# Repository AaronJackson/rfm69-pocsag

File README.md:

# RFM69 Pager Transmitter

This is a relatively complete project for building a DIY pager transmitter using 
an Adafruit Feather LoRa board and ESP8266. Two microcontrollers are used to enable
full remote shutdown of the transmitter. This repo contains the following,

* Code for an ESP8266, which acts as a bridge between MQTT and the Adafruit LoRa
  board. This simply writes out the MQTT messages to UART.
* Code for an Adafruit LoRa (433MHz variant) board, which configures the RFM69 to
  transmit FSK and perform the POCSAG encoding. This is mostly based around a
  modified [pocsag-tool](https://github.com/hazardousfirmware/pocsag-tool/blob/main/pocsag.c)
  by hazardousfirmware (Thank you!)
* A KiCAD PCB for connecting up the ESP8266 and AdaFruit Feather boards. It includes
  a separate voltage regulator, which taps the 5v from the Feather. The ESP8266 pulls
  the Feather's enable pin to ground, which shuts off its 3.3v regulator.
* A quick laser cut box designed with MakerCase and Inkscape. The final version ended
  up being slightly different I think after some tweaking next to the laser cutter.

I have two deployments of this now:

- At home, using my callsign M6PIU.
- At Nottingham Hackspace, using the FAC callsign MB7PNH (Pager NottingHack).

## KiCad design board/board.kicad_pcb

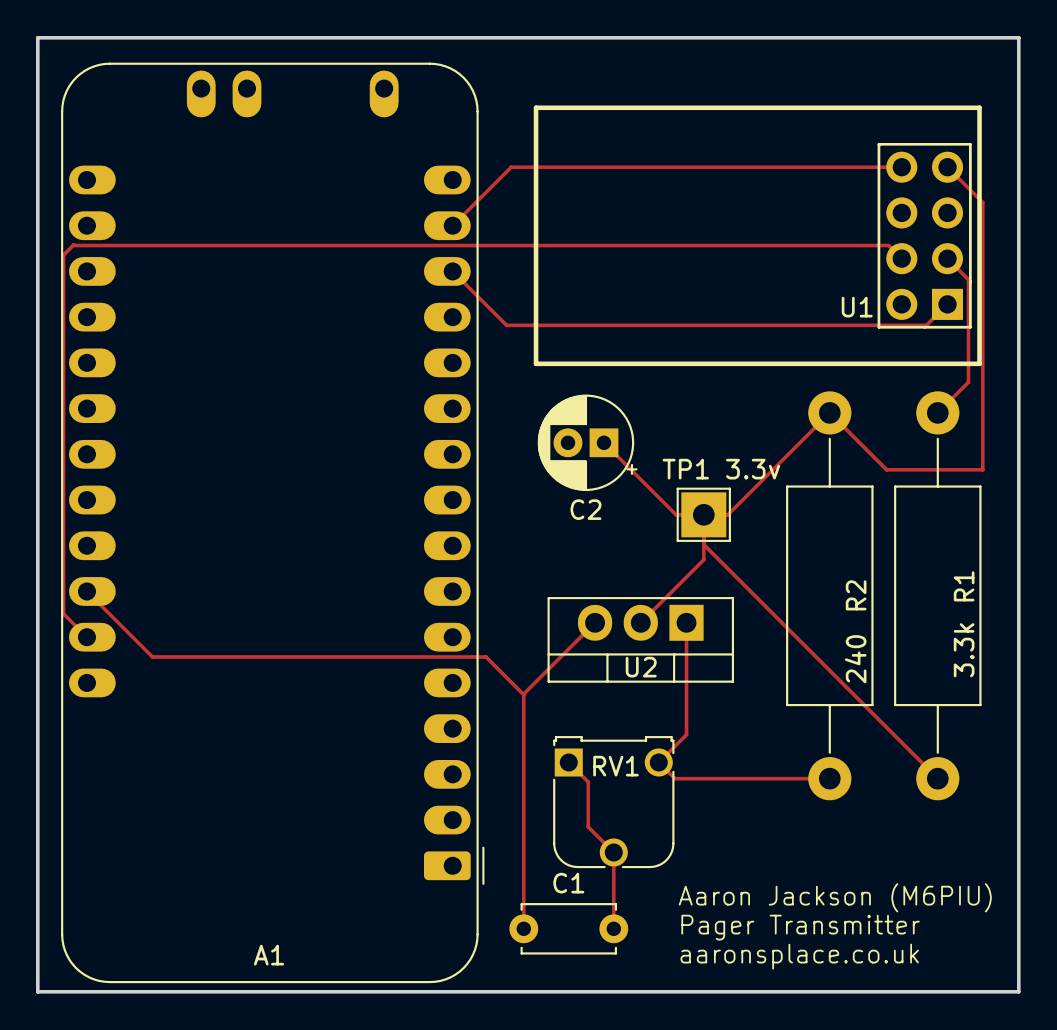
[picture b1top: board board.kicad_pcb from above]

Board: 2 copper layers, 54.5 x 53.0 mm, 9 parts (0 on the bottom side), 8 nets.

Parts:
A1: Adafruit_Feather_32u4_Lora433MHz; Adafruit_Feather_32u4_RFM
C1: 0.1u; C_Disc_D5.0mm_W2.5mm_P5.00mm
C2: 1u; CP_Radial_D5.0mm_P2.00mm
R1: 3.3k; R_Axial_DIN0414_L11.9mm_D4.5mm_P20.32mm_Horizontal
R2: 240; R_Axial_DIN0414_L11.9mm_D4.5mm_P20.32mm_Horizontal
RV1: 5k; Potentiometer_Runtron_RM-065_Vertical
TP1 3.3v: Keystone 4952; TestPoint_THTPad_2.5x2.5mm_Drill1.2mm
U1: ESP-01v090; ESP-01
U2: LM317_TO-220; TO-220-3_Vertical

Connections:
3.3V: C2.1, R1.1, R2.1, TP1 3.3v.1, U1.7 (VCC), U2.2 (VO)
5V: A1.26 (USB), C1.1, U2.3 (VI)
ENABLE_FEATHER: A1.27 (EN), U1.4 (GPIO2)
ESP_RX: A1.15 (TX/D1), U1.8 (URXD)
ESP_TX: A1.14 (RX/D0), U1.1 (UTXD)
GND: A1.4 (GND), C1.2, C2.2, RV1.1, RV1.2, U1.2 (GND)
unnamed: R1.2, U1.3 (CH_PD)
unnamed: R2.2, RV1.3, U2.1 (ADJ)

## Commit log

2024-03-27 Some initial notes
2024-03-28 Correct value for RegBitrateMsb
2024-03-28 Add section on continuous / unlimited sized payloads
2024-03-28 Remove html build - oops
2024-03-29 FIFO buffers and sync data
2024-03-29 Simple example which tx callsign to RIC 6
2024-03-30 Add modified version of https://github.com/hazardousfirmware/pocsag-tool
2024-03-30 Add serial interface and pocsag encoding
2024-03-30 add esp8266 to bridge mqtt to adafruit feather
2024-04-01 bug fix for 13,14,15 character messages ...
2024-04-06 add pcb to put it all together
2024-04-15 Remote power control
2024-04-15 add waitCAD
2024-04-15 Add some stats for mqtt pocsag/status
2024-04-29 Add basic readme
2024-04-29 Create LICENSE
2024-04-29 Small fixes and improvements which I forgot to commit
